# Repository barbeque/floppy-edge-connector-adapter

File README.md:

# Floppy Adapter v3
This adapter is intended to allow older computers equipped with 5.25" floppy drives using an edge connector to use a 3.5" floppy drive.

For long-term reliability, especially in humid environments or when the adapter is expected to be plugged and unplugged often, it's recommended that you pay extra at fabrication time to get hard gold fingers and a bevel. You can bevel it yourself with sandpaper, if needed.

This project was developed as part of a [leaded solder](https://www.leadedsolder.com/) repair of a Sharp X1turbo, and based on an older board developed for a conversion of a NEC PC-8801mkII.

# Version History
## v3.6 (2025)
Move the silkscreen for the female floppy-drive connector to match the label on the bottom of the board. The label was being ignored by assembly houses and this should help correct this behaviour.

## v3.5 (2022)
Add "drive select" breakout pins on the top. This was done to enable a single HxC to emulate two drives on the NEC PC-8801. Thanks to Frio for requesting and co-operating with the development of this version of the adapter.

## v3.0 (2021)

Original release of this board, fixing mounting issues from previous releases.

# Gerber files
You can get the gerber files from [the releases page](https://github.com/barbeque/floppy-edge-connector-adapter/releases/). My usual fabs are JLCPCB, PCBWay and Osh Park.

You can also [order it directly from the project page on PCBWay](https://www.pcbway.com/project/shareproject/5_25__Floppy_edge_connector_to_34_pin_3_5__floppy_drive_adapter.html), which gives me some PCBWay credit that I can use on future custom board projects.

# Bill of Materials
 * 34-pin female IDC right-angle header (0.100") such as [S9207-ND](https://www.digikey.ca/product-detail/en/sullins-connector-solutions/SFH11-PBPC-D17-RA-BK/S9207-ND/1990100) on DigiKey.

# Assembly instructions
 1. Solder the right-angle IDC connector to the board, such that the plastic part of the connector is on the side of the board reading "mount connector this side."
 2. Install adapter into your ribbon cable. If there is no key "tab" on your computer's connector, check for a red wire on the ribbon cable or a triangle marking on the ribbon cable connector in order to know which pin is "1."
 3. Attach drive to adapter, minding the tab on the right-angle IDC connector to get it the right way around.

# HxC Dual Drive support on PC-8801
Note: this only works on the "v3.5" adapter with drive select pads on the top of it.

A single HxC floppy emulator can emulate two floppy drives at once. This usually "just works," but on the PC-8801 you must wire it a special way using two adapters.

The PC-88 has two separate floppy cables instead of one "bussed" cable. Although most signals are bussed together to the floppy drive, each cable has its own independent drive select signal. Both of those selects are on drive select 0 (DS0) which means that we must put a partially-populated adapter into one of the drives in order to provide "its" DS0 to the HxC as drive select 1 (DS1.)

 1. Solder one adapter fully with a right-angle connector as per the previous instructions.
 2. Solder a DuPont jumper wire onto the "Drive Select 0" (DS0) pad of the second adapter.
 3. Install one adapter into each floppy cable on the PC-8801.
 4. Connect the fully-populated adapter to the HxC, and run the jumper wire from the other into the "DS1" select line on the back of the HxC.

For more guidance, please consult [the HxC forum thread for running two drives on a PC-8801.](https://torlus.com/floppy/forum/viewtopic.php?t=502)

# Tested on
 - NEC PC-8801mkII
 - NEC PC-8801mkIISR
 - Sanyo MBC-555
 - Sharp X1turbo
 - Sharp X1 Twin

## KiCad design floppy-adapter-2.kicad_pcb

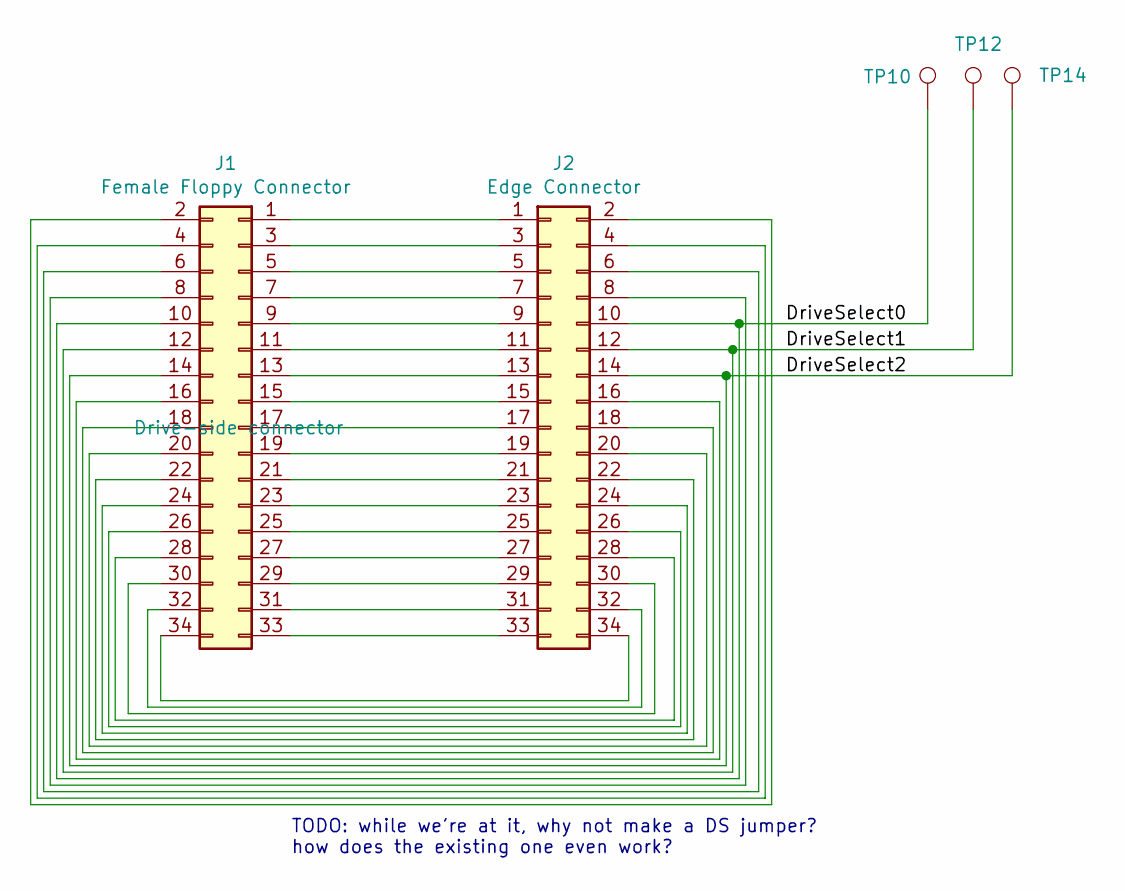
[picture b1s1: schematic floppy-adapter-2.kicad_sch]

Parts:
J1: Female Floppy Connector; Floppy_Connector
J2: Edge Connector; FloppyEdge
TP10, TP12, TP14: TestPoint; TestPoint_Pad_3.0x3.0mm

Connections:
/DriveSelect0: J1.10, J2.10, TP10.1
/DriveSelect1: J1.12, J2.12, TP12.1
/DriveSelect2: J1.14, J2.14, TP14.1
unnamed: J1.1, J2.1
unnamed: J1.2, J2.2
unnamed: J1.3, J2.3
unnamed: J1.4, J2.4
unnamed: J1.5, J2.5
unnamed: J1.6, J2.6
unnamed: J1.7, J2.7
unnamed: J1.8, J2.8
unnamed: J1.9, J2.9
unnamed: J1.11, J2.11
unnamed: J1.13, J2.13
unnamed: J1.15, J2.15
unnamed: J1.16, J2.16
unnamed: J1.17, J2.17
unnamed: J1.18, J2.18
unnamed: J1.19, J2.19
unnamed: J1.20, J2.20
unnamed: J1.21, J2.21
unnamed: J1.22, J2.22
unnamed: J1.23, J2.23
unnamed: J1.24, J2.24
unnamed: J1.25, J2.25
unnamed: J1.26, J2.26
unnamed: J1.27, J2.27
unnamed: J1.28, J2.28
unnamed: J1.29, J2.29
unnamed: J1.30, J2.30
unnamed: J1.31, J2.31
unnamed: J1.32, J2.32
unnamed: J1.33, J2.33
unnamed: J1.34, J2.34

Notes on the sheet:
TODO: while we're at it, why not make a DS jumper? how does the existing one even work?

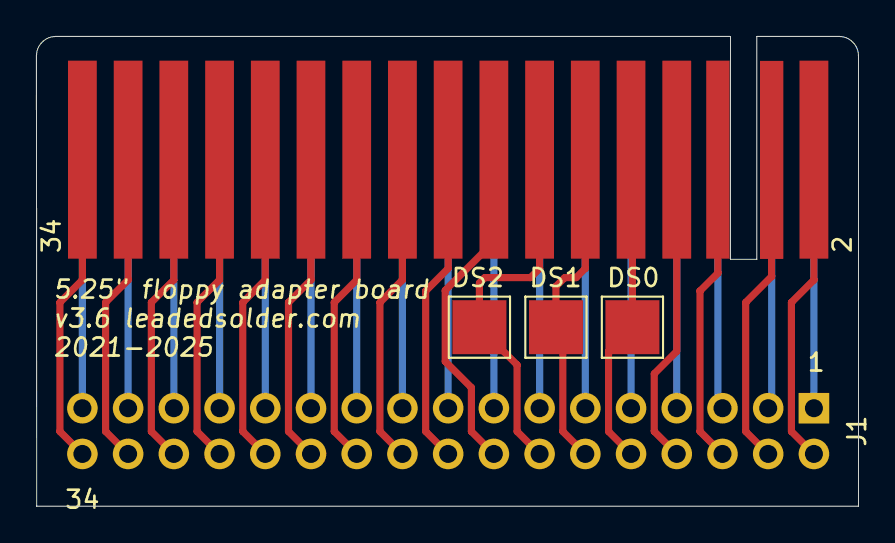
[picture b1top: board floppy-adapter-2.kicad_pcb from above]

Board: 2 copper layers, 45.7 x 26.1 mm, 5 parts (1 on the bottom side), 34 nets.

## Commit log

2021-01-21 Edges fit into a real X1
2021-01-21 footprint numbering
2021-01-21 Edge layer now correct.
2021-01-21 Turn conn around properly
2021-01-21 Update TODO
2021-02-06 Fix my bonehead size mistake
2021-02-09 README and BOM
2021-02-09 Link back to blog
2021-02-10 Releases link
2021-02-10 Create LICENSE
2021-02-12 Remove Sponsors stuff
2021-05-29 Tested on Twin now (thanks Alfredo Henriquez)
2021-06-01 PCBWay link
2022-09-30 KiCad6; expose DS pins, lengthen board
2023-07-31 KiCad 7
2023-07-31 Some extra stuff in the project file got added
2024-02-14 replace pictures
2024-02-14 Dual-drive configuration
2024-02-14 Fix pin1 stripe
2025-01-20 Caution note
2025-01-20 Add Sanyo support
2025-10-17 Flip the silkscreen to the other side for the 34-pin connector, finally
2025-10-17 Revise readme
2025-10-17 nice little chamfer
2025-12-01 Make PCB shorter to avoid bottoming out against the female 34-pin
